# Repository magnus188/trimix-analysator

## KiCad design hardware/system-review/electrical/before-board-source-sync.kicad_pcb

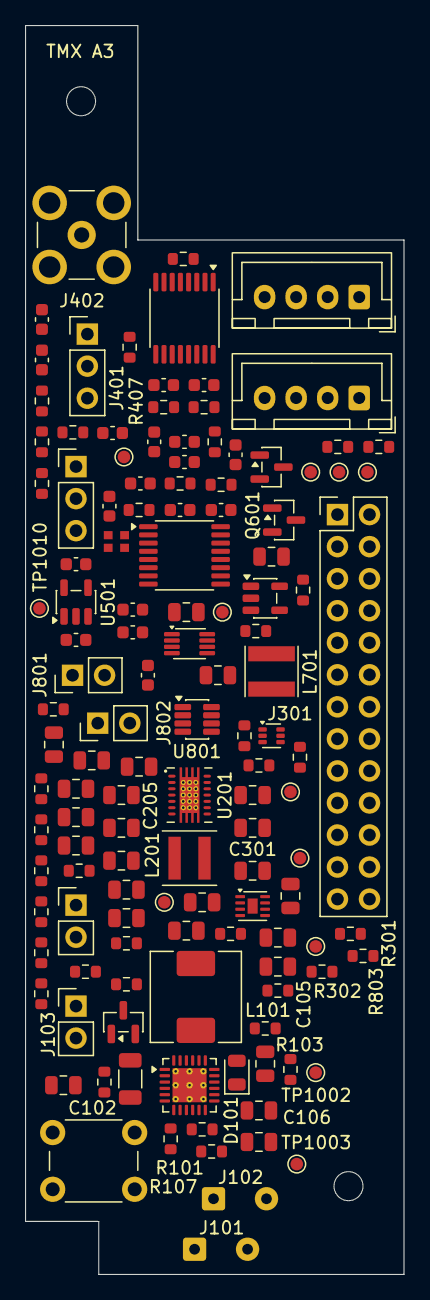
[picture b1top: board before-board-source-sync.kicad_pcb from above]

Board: 4 copper layers, 30.0 x 99.0 mm, 131 parts (0 on the bottom side), 63 nets, no tracks yet.

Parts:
C101: 1u / 25V X7R; C_0805_2012Metric
C102: 10u / 25V X7R; C_1206_3216Metric
C103: 47n / 16V X7R; C_0805_2012Metric
C104, C105, C204, C205, C206: 22u / 10V X7R; C_0805_2012Metric
C106, C201, C202: 10u / 10V X7R; C_0805_2012Metric
C107: 4.7u / 10V X7R; C_0805_2012Metric
C203, C301: 100n / 10V X7R; C_0805_2012Metric
C401, C404, C408, C409, C505, C509: 1u / X7R; C_0603_1608Metric
C402, C403, C405, C406, C506, C507: 10n; C_0603_1608Metric
C407, C504, C508: 100n; C_0603_1608Metric
C501, C502: 4.7u / X7R / 10V; C_0603_1608Metric
C503: 10n / DNP: obsolete bypass; C_0603_1608Metric
C601, C804: 1u / 10V; C_0805_2012Metric
C701: 10u / 10V; C_0805_2012Metric
C702, C703: 22u / 10V; C_0805_2012Metric
C704, C705: 4.7u / 10V; C_0805_2012Metric
C706: 10n / DNP: obsolete bypass; C_0805_2012Metric
C707, C708: 100n; C_0805_2012Metric
C801, C802: 100n / 10V; C_0805_2012Metric
C803: 33n / 10V; C_0805_2012Metric
D101: CHARGE (red); LED_0805_2012Metric
H1, H2: M2 NPTH 2.30; Mechanical_M2_NPTH_2.30mm
J101: FROM USB BOARD (2P); SolderWire-0.25sqmm_1x02_P4.2mm_D0.65mm_OD1.7mm
J102: PACK PIGTAIL; SolderWire-0.25sqmm_1x02_P4.2mm_D0.65mm_OD1.7mm
J103: PACK NTC: 103AT-2; PinHeader_1x02_P2.54mm_Vertical
J104: ARM: OPEN; PinHeader_1x02_P2.54mm_Vertical
J301: GUITION JP1 / 2x13; PinHeader_2x13_P2.54mm_Vertical
J401: AO2 / 3-pin cable; PinHeader_1x03_P2.54mm_Vertical
J402: SMB Male PCB / verify fit; SMB_Jack_Vertical
J501: MD62 cable / <=30 cm; PinHeader_1x03_P2.54mm_Vertical
J601: BME280 harness; JST_XH_B4B-XH-A_1x04_P2.50mm_Vertical
J701: ZE07-CO harness; JST_XH_B4B-XH-A_1x04_P2.50mm_Vertical
J801: POWER BUTTON / 1NO; PinHeader_1x02_P2.54mm_Vertical
J802: BUTTON LED +/-; PinHeader_1x02_P2.54mm_Vertical
L101: 1u / Isat >= 4.5A; L_Wuerth_HCM-7050
L201: 1.5u / XFL4020-152ME; L_Coilcraft_XxL4020
L701: 1uH / Isat >= 5 A; L_Taiyo-Yuden_NR-40xx
Q101: 2N7002; SOT-23
Q601, Q602: BSS138; SOT-23
R101: 5.23k 1%; R_0603_1608Metric
R102: 30.1k 1%; R_0603_1608Metric
R103: 620R 1%; R_0603_1608Metric
R104, R105, R203, R501, R703, R803: 100k; R_0603_1608Metric
R106: 2.2k; R_0603_1608Metric
R107, R301, R802: 10k; R_0603_1608Metric
R201: 1.62M 1%; R_0603_1608Metric
R202: 180k 1%; R_0603_1608Metric
R302, R303: 4.7k / FIT; R_0603_1608Metric
R401, R402, R405, R406: 100R / 0.1%; R_0603_1608Metric
R403, R404, R407, R408: 1M / 1%; R_0603_1608Metric
R409, R410, R504, R505: 10k / 0.1%; R_0603_1608Metric
R506, R507: 680R / 0.1%; R_0603_1608Metric
R601: 0R / fit: 3.3 V; R_0603_1608Metric
R602: 0R / DNP: 5 V option; R_0603_1608Metric
R603, R604: 4.7k / DNP; R_0603_1608Metric
R701: 787k / 0.1%; R_0603_1608Metric
R702: 100k / 0.1%; R_0603_1608Metric
R704, R705: 100R; R_0603_1608Metric
R801: 5.1k; R_0603_1608Metric
R804: 1k / DNP; R_0603_1608Metric
RN501: 2x2k / 1:1 matched; Vishay_ACAS0606_AT_IEC
SW101: BQ wake / reset; SW_PUSH_6mm
TP1001: GND; TestPoint_Pad_D1.0mm
TP1002: USB_5V; TestPoint_Pad_D1.0mm
TP1003: PACK_P; TestPoint_Pad_D1.0mm
TP1004: VSYS; TestPoint_Pad_D1.0mm
TP1005: VOUT_5V; TestPoint_Pad_D1.0mm
TP1006: HOST_3V3; TestPoint_Pad_D1.0mm
TP1007: POWER_EN; TestPoint_Pad_D1.0mm
TP1008: I2C_SCL; TestPoint_Pad_D1.0mm
TP1009: I2C_SDA; TestPoint_Pad_D1.0mm
TP1010: HE_3V0; TestPoint_Pad_D1.0mm
TP1011: HE_SENSE; TestPoint_Pad_D1.0mm
TP1012: O2_VMID; TestPoint_Pad_D1.0mm
U101: BQ25895RTWR; Texas_RTW_WQFN-24-1EP_4x4mm_P0.5mm_EP2.7x2.7mm_ThermalVias
U201: TPS63020DSJR; TI_DSJ_14
U301: MAX17048G+; TDFN-8-1EP_2x2mm_P0.5mm_EP0.8x1.2mm
U401, U502: ADS122C04IPWR; TSSOP-16_4.4x5mm_P0.65mm
U501, U702: TPS7A2030PDBVR; SOT-23-5
U701: TPS61023DRLR; SOT-563
U703: TXU0202DCUR; VSSOP-8_2.3x2mm_P0.5mm
U801: LTC2954CTS8-1; TSOT-23-8

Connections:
/01 CHARGING + BATTERY/BQ_BTST: C103.2, U101.21
/01 CHARGING + BATTERY/BQ_ILIM: R103.1, U101.10
/01 CHARGING + BATTERY/BQ_PMID: C102.1, U101.23
/01 CHARGING + BATTERY/BQ_QON_N: SW101.1, U101.12
/01 CHARGING + BATTERY/BQ_REGN: C107.1, R101.1, U101.22
/01 CHARGING + BATTERY/BQ_SW: C103.1, L101.1, U101.19, U101.20
/01 CHARGING + BATTERY/CHG_CE_N: Q101.3, R104.2, U101.9
/01 CHARGING + BATTERY/CHG_STAT_N: D101.1, U101.4
/01 CHARGING + BATTERY/PACK_TS: J103.1, R101.2, R102.1, U101.11
/02 SWITCHED 5 V/TPS_FB: R201.2, R202.1, U201.3
/02 SWITCHED 5 V/TPS_VINA: C203.1, U201.1
BME_SCL: J601.3, Q601.3, R603.2
BME_SDA: J601.4, Q602.3, R604.2
BME_VIN: C601.1, J601.1, R601.2, R602.2, R603.1, R604.1
BUTTON_LED_A: J802.1, R804.2
CHARGE_ARM: J104.2, Q101.1, R105.1
CHG_INT_N: J301.13, R107.2, U101.7
CO_5V28: C702.1, C703.1, J701.1, R701.1, U701.6
CO_FB: R701.2, R702.1, U701.1
CO_LOGIC_3V0: C705.1, C708.1, U702.5, U703.7
CO_RX_3V0: R705.1, U703.8
CO_RX_CABLE: J701.4, R705.2
CO_SW: L701.2, U701.5
CO_TX_3V0: R704.1, U703.1
CO_TX_CABLE: J701.3, R704.2
CO_UART_EN: J301.9, R703.1, U703.6
CO_UART_RX: J301.10, U703.4
CO_UART_TX: J301.12, U703.5
GAUGE_ALERT_N: J301.11, R301.2, U301.5
GND: C101.2, C102.2, C104.2, C105.2, C106.2, C107.2, C201.2, C202.2, C203.2, C204.2, C205.2, C206.2, C301.2, C402.2, C403.2, C405.2, C406.2, C407.2, C408.2, C409.2, C501.2, C502.2, C503.2, C504.2, C506.2, C507.2, C508.2, C509.2, C601.2, C701.2, C702.2, C703.2, C704.2, C705.2, C706.2, C707.2, C708.2, C801.2, C802.2, C803.2, C804.2, J101.2, J102.2, J103.2, J301.5, J301.6, J301.16, J501.3, J601.2, J701.2, J801.2, J802.2, Q101.2, R102.2, R103.2, R105.2, R202.2, R410.2, R501.2, R505.2, R702.2, R703.2, RN501.3, SW101.2, TP1001.1, U101.8, U101.17, U101.18, U101.25, U201.2, U201.15, U301.1, U301.4, U301.6, U301.9, U401.1, U401.2, U401.4, U401.5, U501.2, U502.2, U502.4, U502.5, U701.4, U702.2, U703.2, U801.4
HE_3V0: C502.1, J501.1, R504.1, RN501.1, TP1010.1, U501.5
HE_AIN_N: C505.2, C507.1, R507.2, U502.10
HE_AIN_P: C505.1, C506.1, R506.2, U502.11
HE_ENABLE: J301.17, R501.1, U501.3
HE_EXC_DIV: C504.1, R504.2, R505.1, U502.7
HE_REF: R506.1, RN501.2, RN501.4
HE_SENSE: J501.2, R507.1, TP1011.1
HOST_3V3: C407.1, C408.1, C508.1, C509.1, C707.1, J301.1, J301.3, J301.18, Q601.1, Q602.1, R107.1, R301.1, R302.1, R303.1, R409.1, R601.1, R802.1, R803.1, TP1006.1, U401.3, U401.12, U401.13, U502.1, U502.3, U502.12, U502.13, U703.3
I2C_SCL: J301.14, Q601.2, R302.2, TP1008.1, U101.5, U301.7, U401.16, U502.16
I2C_SDA: J301.21, Q602.2, R303.2, TP1009.1, U101.6, U301.8, U401.15, U502.15
unnamed: D101.2, R106.1
unnamed: J801.1, R801.1
unnamed: L201.1, U201.8, U201.9
unnamed: L201.2, U201.6, U201.7
unnamed: C803.1, U801.3
unnamed: C804.1, U801.7
O2_A_AIN_N: C401.1, C402.1, R401.2, R403.1, U401.10
O2_A_AIN_P: C401.2, C403.1, R402.2, R404.2, U401.11
O2_A_RAW_N: J401.2, R401.1
O2_A_RAW_P: J401.1, R402.1
O2_B_AIN_N: C404.1, C405.1, R405.2, R407.1, U401.6
O2_B_AIN_P: C404.2, C406.1, R406.2, R408.2, U401.7
O2_B_RAW_N: J402.2, R405.1
O2_B_RAW_P: J402.1, R406.1
O2_VMID: C409.1, R403.2, R404.1, R407.2, R408.1, R409.2, R410.1, TP1012.1, U502.6
PACK_P: C106.1, C301.1, J102.1, TP1003.1, U101.13, U101.14, U301.2, U301.3
PB_FILTERED_N: C802.1, R801.2, U801.2
POWER_EN: R203.2, TP1007.1, U201.12, U801.6
POWER_INT_N: J301.19, R802.2, U801.5
POWER_KILL_N: J301.8, R803.2, U801.8
USB_5V: C101.1, J101.1, TP1002.1, U101.1
VOUT_5V: C204.1, C205.1, C206.1, C501.1, C701.1, C704.1, J301.2, J301.4, L701.1, R201.1, R602.1, R804.1, TP1005.1, U201.4, U201.5, U501.1, U701.2, U701.3, U702.1, U702.3
VSYS: C104.1, C105.1, C201.1, C202.1, C801.1, J104.1, L101.2, R104.1, R106.2, R203.1, TP1004.1, U101.15, U101.16, U201.10, U201.11, U201.13, U801.1

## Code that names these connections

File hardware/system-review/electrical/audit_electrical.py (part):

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    'CO_UART_RX': (10, 31, 'host input', '9600 baud, TXU0202 A2Y'),
    'POWER_INT_N': (19, 32, 'host input', 'active-low button interrupt'),
    'POWER_KILL_N': (8, 33, 'host open drain', 'assert low to shut down; release during boot'),
    'HE_ENABLE': (17, 34, 'host output', 'default low; GPIO34 JTAG strap caveat'),
    'CHG_INT_N': (13, 49, 'host input', 'shared active-low BQ interrupt + permission-absent feedback'),
    'USB_ILIM_AUTH': (11, 50, 'host output', 'fail-low source-current permission; fresh rising edge after qualification'),
    'CO_UART_EN': (9, 51, 'host output', 'default low until translated supplies valid'),
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    check('Upstream default selected19.1k standard resistor',components['R119'].findtext('value').startswith('19.1k') and r119_fields.get('MPN')=='RT0402BRD0719K1L')
    check('Qualified parallel resistor1k',components['R116'].findtext('value').startswith('1k'))
    for pad in ('A4','A9','B4','B9'):
        check(f'USB {pad} VBUS', pins[('J901',pad)] == 'USB_5V')
    for ref,val in [('R121','34k'),('R122','649R'),('R123','10k')]:
        fields={q.get('name'):q.text or ''for q in components[ref].findall('./fields/field')}
        check(ref+' OVLO precise value/TCR',components[ref].findtext('value').startswith(val) and fields.get('MPN','').endswith('BYEA'))
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    check('SMB shell has no ground connection', ('J402','2') not in nets['GND'])
    check('TPS VINA internal-feed filter only', nets[pins[('U201','1')]] == {('U201','1'),('C203','1')})
    check('Charger cannot be firmware-armed by spare GPIO',
          not any(ref=='J301' for ref, pin in nets['CHARGE_ARM']))
    for ref in ('R506','R507'):
        check(f'{ref} fault current resistor', components[ref].findtext('value') == '680R / 0.1%')
    for ref in ('R602','R603','R604','R804'):
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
